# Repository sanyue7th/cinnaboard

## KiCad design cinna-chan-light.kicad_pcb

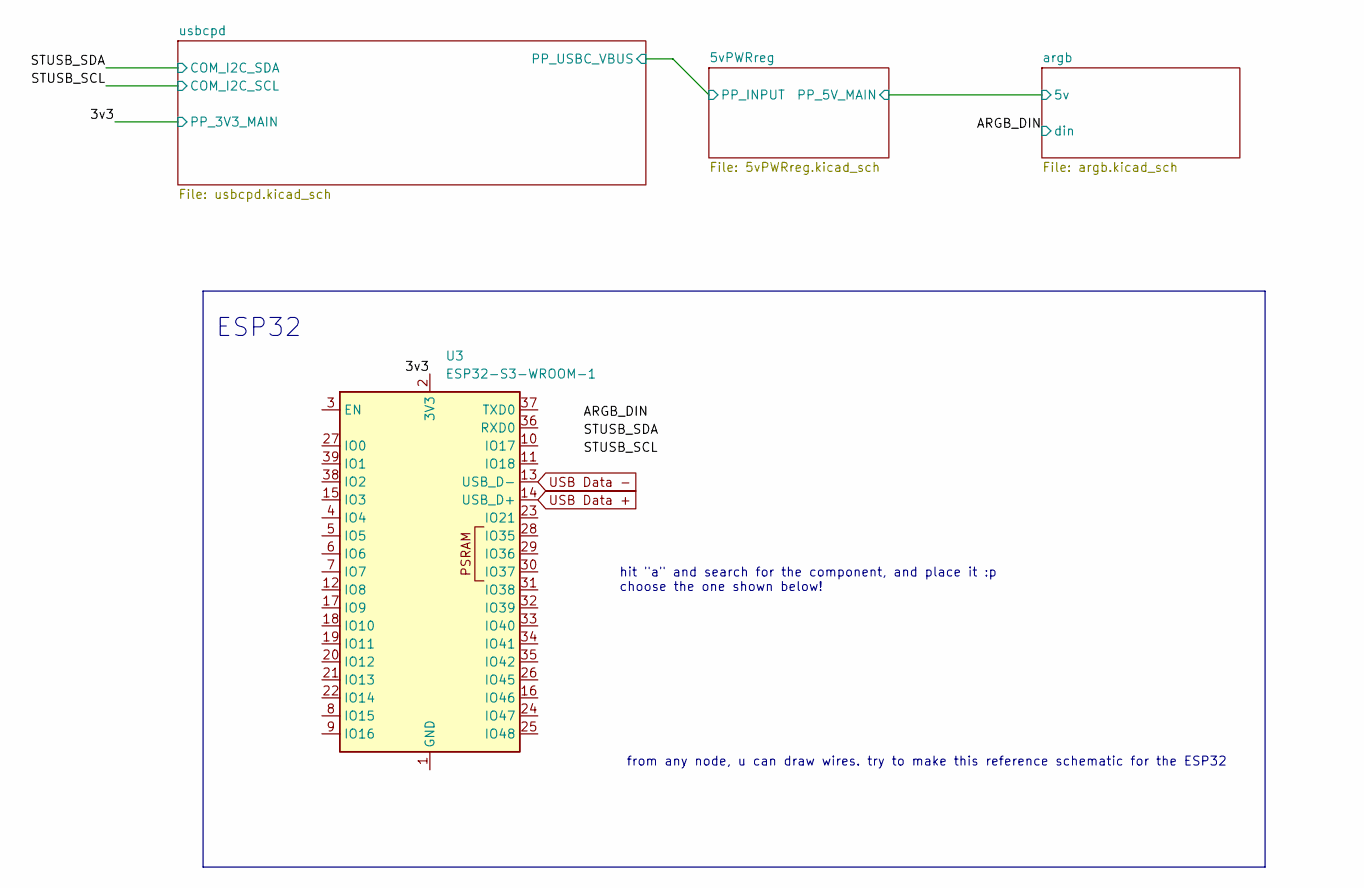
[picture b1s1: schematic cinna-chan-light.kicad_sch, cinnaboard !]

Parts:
U3: ESP32-S3-WROOM-1; LCSC C2913192

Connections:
unnamed: U3.1 (GND), U3.40 (GND), U3.41 (GND)

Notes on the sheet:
hit "a" and search for the component, and place it :p choose the one shown below!
ESP32
from any node, u can draw wires. try to make this reference schematic for the ESP32

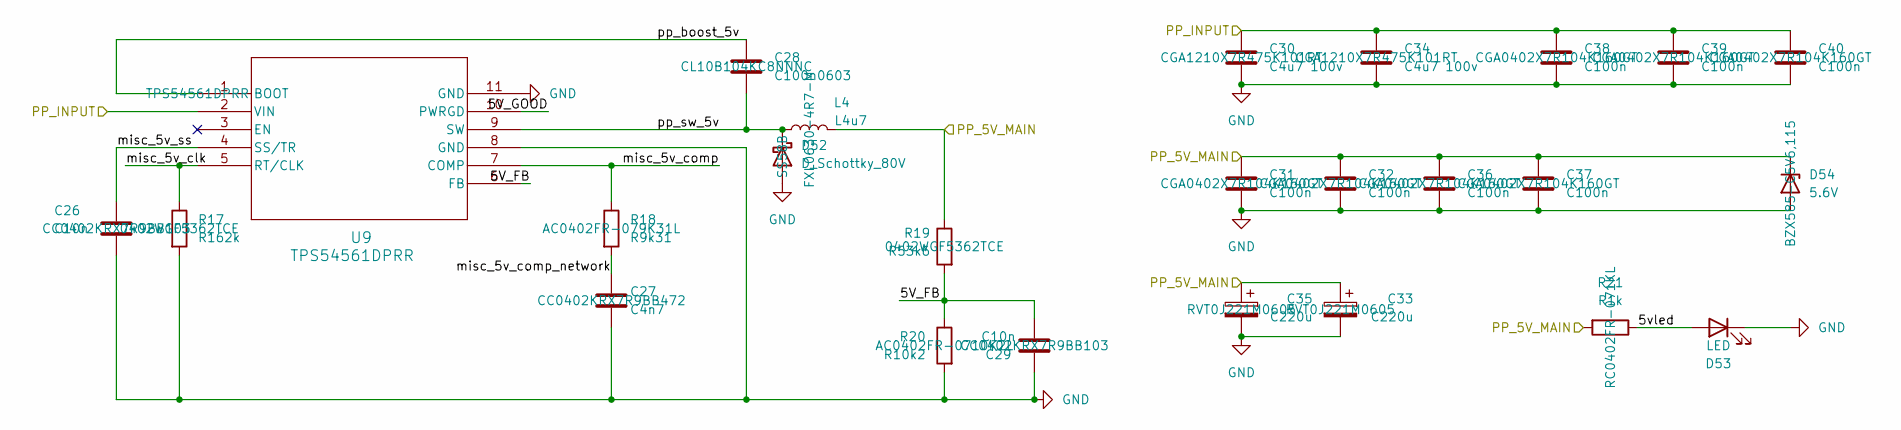
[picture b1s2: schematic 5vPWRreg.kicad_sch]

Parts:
C26, C29: C10n; C_0402_1005Metric
C27: C4n7; C_0402_1005Metric
C28: C100n0603; C_0603_1608Metric
C30, C34: C4u7 100v; L_1210_3225Metric
C31, C32, C36, C37, C38, C39, C40: C100n; C_0402_1005Metric
C33, C35: C220u; CP_Elec_6.3x5.4
D52: D_Schottky_80V; D_SMB
D53: LED; LED_0603_1608Metric
D54: 5.6V; D_SOD-523
L4: L4u7; L_Sunlord_MWSA0603S
R17: R162k; R_0402_1005Metric
R18: R9k31; R_0402_1005Metric
R19: R53k6; R_0402_1005Metric
R20: R10k2; R_0402_1005Metric
R21: R1k; R_0402_1005Metric
U9: TPS54561DPRR; WSON10_DPR_TEX

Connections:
/5vPWRreg/5V_FB: C29.1, R19.2, R20.1, U9.6 (FB)
/5vPWRreg/5V_GOOD: U9.10 (PWRGD)
/5vPWRreg/5vled: D53.2 (A), R21.1
/5vPWRreg/PP_5V_MAIN: C31.1, C32.1, C33.1, C35.1, C36.1, C37.1, D54.1 (K), L4.2, R19.1, R21.2; also elsewhere on the board
/5vPWRreg/PP_INPUT: C30.1, C34.1, C38.1, C39.1, C40.1, U9.2 (VIN)
/5vPWRreg/misc_5v_clk: R17.1, U9.5 (RT/CLK)
/5vPWRreg/misc_5v_comp: R18.1, U9.7 (COMP)
/5vPWRreg/misc_5v_comp_network: C27.2, R18.2
/5vPWRreg/misc_5v_ss: C26.2, U9.4 (SS/TR)
/5vPWRreg/pp_boost_5v: C28.1, U9.1 (BOOT)
/5vPWRreg/pp_sw_5v: C28.2, D52.1 (K), L4.1, U9.9 (SW)
GND: C26.1, C27.1, C29.2, C30.2, C31.2, C32.2, C33.2, C34.2, C35.2, C36.2, C37.2, C38.2, C39.2, C40.2, D52.2 (A), D53.1 (K), D54.2 (A), R17.2, R20.2, U9.8 (GND), U9.11 (GND); also elsewhere on the board

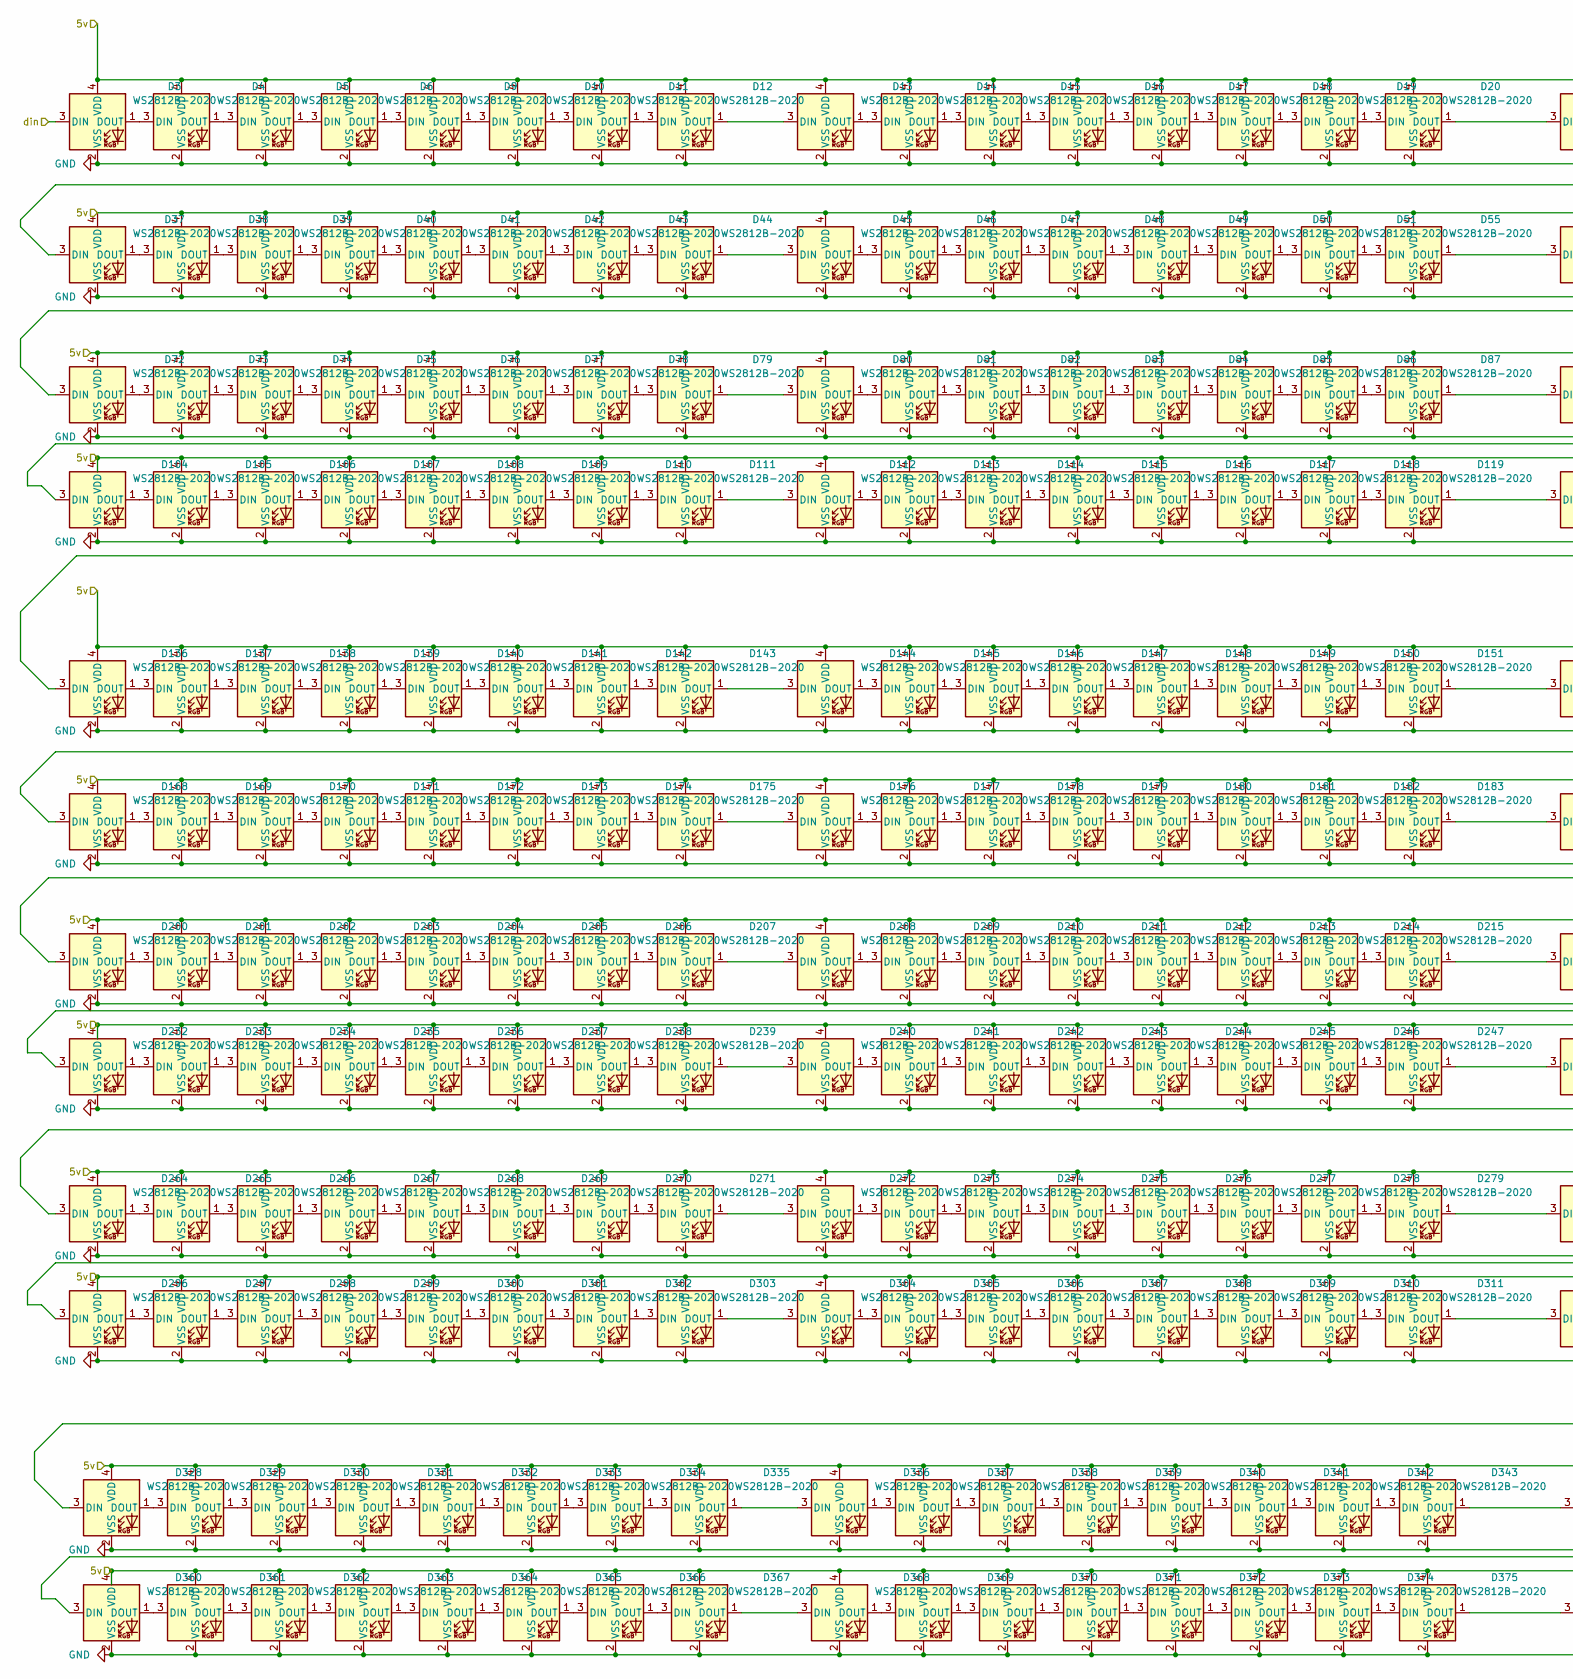
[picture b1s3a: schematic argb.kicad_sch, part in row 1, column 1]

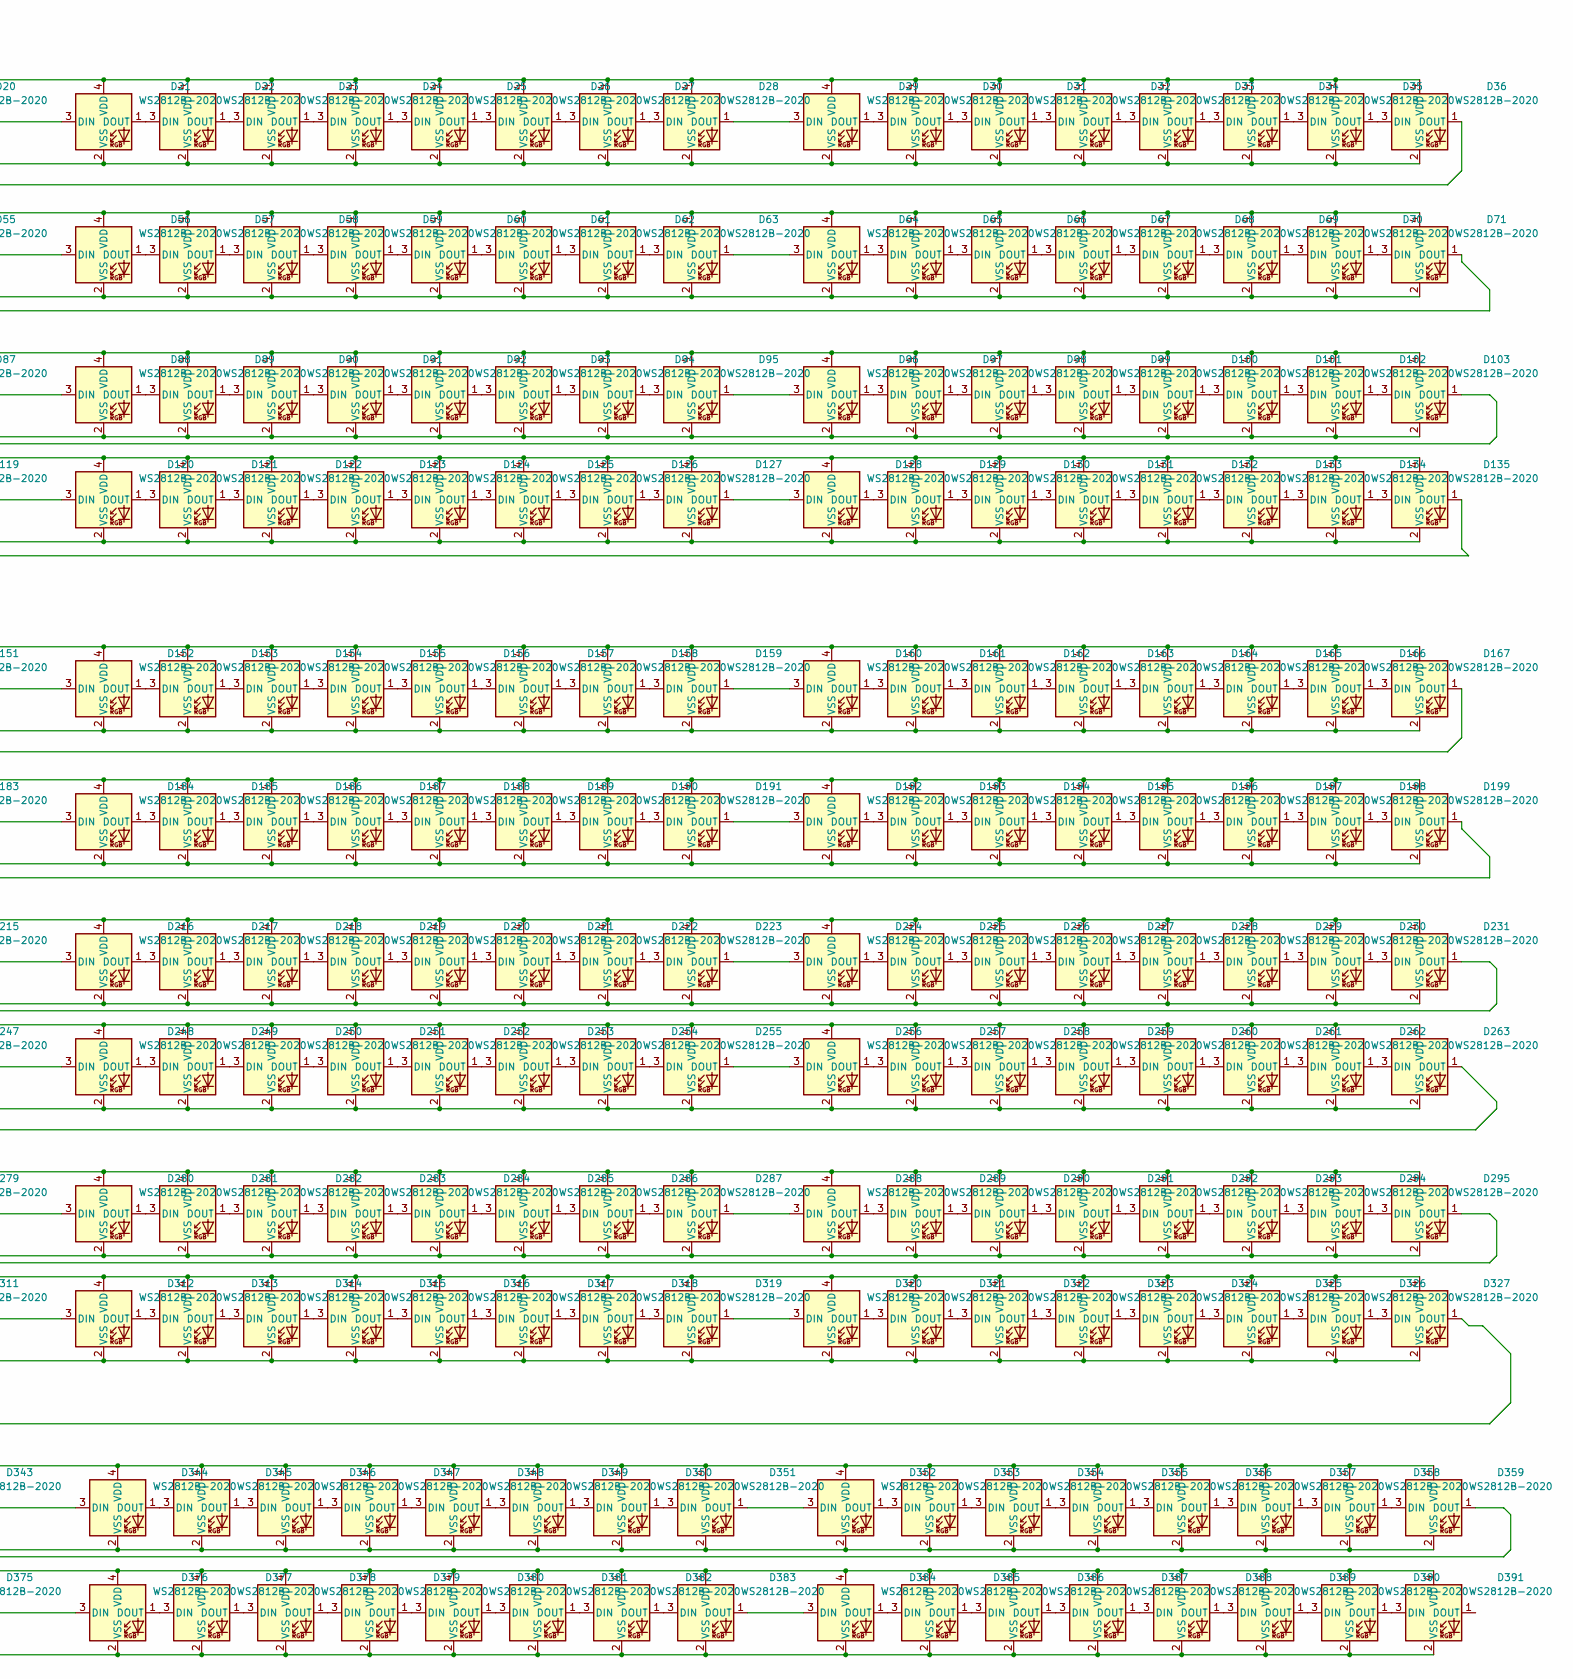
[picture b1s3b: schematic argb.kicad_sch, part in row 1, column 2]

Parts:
D3, D4, D5, D6, D9, D10, D11, D12, D13, D14, D15, D16, D17, D18, D19, D20, D21, D22, D23, D24, D25, D26, D27, D28, D29, D30, D31, D32, D33, D34, D35, D36, D37, D38, D39, D40, D41, D42, D43, D44, D45, D46, D47, D48, D49, D50, D51, D55, D56, D57, D58, D59, D60, D61, D62, D63, D64, D65, D66, D67, D68, D69, D70, D71, D72, D73, D74, D75, D76, D77, D78, D79, D80, D81, D82, D83, D84, D85, D86, D87, D88, D89, D90, D91, D92, D93, D94, D95, D96, D97, D98, D99, D100, D101, D102, D103, D104, D105, D106, D107, D108, D109, D110, D111, D112, D113, D114, D115, D116, D117, D118, D119, D120, D121, D122, D123, D124, D125, D126, D127, D128, D129, D130, D131, D132, D133, D134, D135, D136, D137, D138, D139, D140, D141, D142, D143, D144, D145, D146, D147, D148, D149, D150, D151, D152, D153, D154, D155, D156, D157, D158, D159, D160, D161, D162, D163, D164, D165, D166, D167, D168, D169, D170, D171, D172, D173, D174, D175, D176, D177, D178, D179, D180, D181, D182, D183, D184, D185, D186, D187, D188, D189, D190, D191, D192, D193, D194, D195, D196, D197, D198, D199, D200, D201, D202, D203, D204, D205, D206, D207, D208, D209, D210, D211, D212, D213, D214, D215, D216, D217, D218, D219, D220, D221, D222, D223, D224, D225, D226, D227, D228, D229, D230, D231, D232, D233, D234, D235, D236, D237, D238, D239, D240, D241, D242, D243, D244, D245, D246, D247, D248, D249, D250, D251, D252, D253, D254, D255, D256, D257, D258, D259, D260, D261, D262, D263, D264, D265, D266, D267, D268, D269, D270, D271, D272, D273, D274, D275, D276, D277, D278, D279, D280, D281, D282, D283, D284, D285, D286, D287, D288, D289, D290, D291, D292, D293, D294, D295, D296, D297, D298, D299, D300, D301, D302, D303, D304, D305, D306, D307, D308, D309, D310, D311, D312, D313, D314, D315, D316, D317, D318, D319, D320, D321, D322, D323, D324, D325, D326, D327, D328, D329, D330, D331, D332, D333, D334, D335, D336, D337, D338, D339, D340, D341, D342, D343, D344, D345, D346, D347, D348, D349, D350, D351, D352, D353, D354, D355, D356, D357, D358, D359, D360, D361, D362, D363, D364, D365, D366, D367, D368, D369, D370, D371, D372, D373, D374, D375, D376, D377, D378, D379, D380, D381, D382, D383, D384, D385, D386, D387, D388, D389, D390, D391: WS2812B-2020; LED_WS2812B-2020_PLCC4_2.0x2.0mm

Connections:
/5vPWRreg/PP_5V_MAIN: D3.4 (VDD), D4.4 (VDD), D5.4 (VDD), D6.4 (VDD), D9.4 (VDD), D10.4 (VDD), D11.4 (VDD), D12.4 (VDD), D13.4 (VDD), D14.4 (VDD), D15.4 (VDD), D16.4 (VDD), D17.4 (VDD), D18.4 (VDD), D19.4 (VDD), D20.4 (VDD), D21.4 (VDD), D22.4 (VDD), D23.4 (VDD), D24.4 (VDD), D25.4 (VDD), D26.4 (VDD), D27.4 (VDD), D28.4 (VDD), D29.4 (VDD), D30.4 (VDD), D31.4 (VDD), D32.4 (VDD), D33.4 (VDD), D34.4 (VDD), D35.4 (VDD), D36.4 (VDD), D37.4 (VDD), D38.4 (VDD), D39.4 (VDD), D40.4 (VDD), D41.4 (VDD), D42.4 (VDD), D43.4 (VDD), D44.4 (VDD), D45.4 (VDD), D46.4 (VDD), D47.4 (VDD), D48.4 (VDD), D49.4 (VDD), D50.4 (VDD), D51.4 (VDD), D55.4 (VDD), D56.4 (VDD), D57.4 (VDD), D58.4 (VDD), D59.4 (VDD), D60.4 (VDD), D61.4 (VDD), D62.4 (VDD), D63.4 (VDD), D64.4 (VDD), D65.4 (VDD), D66.4 (VDD), D67.4 (VDD), D68.4 (VDD), D69.4 (VDD), D70.4 (VDD), D71.4 (VDD), D72.4 (VDD), D73.4 (VDD), D74.4 (VDD), D75.4 (VDD), D76.4 (VDD), D77.4 (VDD), D78.4 (VDD), D79.4 (VDD), D80.4 (VDD), D81.4 (VDD), D82.4 (VDD), D83.4 (VDD), D84.4 (VDD), D85.4 (VDD), D86.4 (VDD), D87.4 (VDD), D88.4 (VDD), D89.4 (VDD), D90.4 (VDD), D91.4 (VDD), D92.4 (VDD), D93.4 (VDD), D94.4 (VDD), D95.4 (VDD), D96.4 (VDD), D97.4 (VDD), D98.4 (VDD), D99.4 (VDD), D100.4 (VDD), D101.4 (VDD), D102.4 (VDD), D103.4 (VDD), D104.4 (VDD), D105.4 (VDD), D106.4 (VDD), D107.4 (VDD), D108.4 (VDD), D109.4 (VDD), D110.4 (VDD), D111.4 (VDD), D112.4 (VDD), D113.4 (VDD), D114.4 (VDD), D115.4 (VDD), D116.4 (VDD), D117.4 (VDD), D118.4 (VDD), D119.4 (VDD), D120.4 (VDD), D121.4 (VDD), D122.4 (VDD), D123.4 (VDD), D124.4 (VDD), D125.4 (VDD), D126.4 (VDD), D127.4 (VDD), D128.4 (VDD), D129.4 (VDD), D130.4 (VDD), D131.4 (VDD), D132.4 (VDD), D133.4 (VDD), D134.4 (VDD), D135.4 (VDD), D136.4 (VDD), D137.4 (VDD), D138.4 (VDD), D139.4 (VDD), D140.4 (VDD), D141.4 (VDD), D142.4 (VDD), D143.4 (VDD), D144.4 (VDD), D145.4 (VDD), D146.4 (VDD), D147.4 (VDD), D148.4 (VDD), D149.4 (VDD), D150.4 (VDD), D151.4 (VDD), D152.4 (VDD), D153.4 (VDD), D154.4 (VDD), D155.4 (VDD), D156.4 (VDD), D157.4 (VDD), D158.4 (VDD), D159.4 (VDD), D160.4 (VDD), D161.4 (VDD), D162.4 (VDD), D163.4 (VDD), D164.4 (VDD), D165.4 (VDD), D166.4 (VDD), D167.4 (VDD), D168.4 (VDD), D169.4 (VDD), D170.4 (VDD), D171.4 (VDD), D172.4 (VDD), D173.4 (VDD), D174.4 (VDD), D175.4 (VDD), D176.4 (VDD), D177.4 (VDD), D178.4 (VDD), D179.4 (VDD), D180.4 (VDD), D181.4 (VDD), D182.4 (VDD), D183.4 (VDD), D184.4 (VDD), D185.4 (VDD), D186.4 (VDD), D187.4 (VDD), D188.4 (VDD), D189.4 (VDD), D190.4 (VDD), D191.4 (VDD), D192.4 (VDD), D193.4 (VDD), D194.4 (VDD), D195.4 (VDD), D196.4 (VDD), D197.4 (VDD), D198.4 (VDD), D199.4 (VDD), D200.4 (VDD), D201.4 (VDD), D202.4 (VDD), D203.4 (VDD), D204.4 (VDD), D205.4 (VDD), D206.4 (VDD), D207.4 (VDD), D208.4 (VDD), D209.4 (VDD), D210.4 (VDD), D211.4 (VDD), D212.4 (VDD), D213.4 (VDD), D214.4 (VDD), D215.4 (VDD), D216.4 (VDD), D217.4 (VDD), D218.4 (VDD), D219.4 (VDD), D220.4 (VDD), D221.4 (VDD), D222.4 (VDD), D223.4 (VDD), D224.4 (VDD), D225.4 (VDD), D226.4 (VDD), D227.4 (VDD), D228.4 (VDD), D229.4 (VDD), D230.4 (VDD), D231.4 (VDD), D232.4 (VDD), D233.4 (VDD), D234.4 (VDD), D235.4 (VDD), D236.4 (VDD), D237.4 (VDD), D238.4 (VDD), D239.4 (VDD), D240.4 (VDD), D241.4 (VDD), D242.4 (VDD), D243.4 (VDD), D244.4 (VDD), D245.4 (VDD), D246.4 (VDD), D247.4 (VDD), D248.4 (VDD), D249.4 (VDD), D250.4 (VDD), D251.4 (VDD), D252.4 (VDD), D253.4 (VDD), D254.4 (VDD), D255.4 (VDD), D256.4 (VDD), D257.4 (VDD), D258.4 (VDD), D259.4 (VDD), D260.4 (VDD), D261.4 (VDD), D262.4 (VDD), D263.4 (VDD), D264.4 (VDD), D265.4 (VDD), D266.4 (VDD), D267.4 (VDD), D268.4 (VDD), D269.4 (VDD), D270.4 (VDD), D271.4 (VDD), D272.4 (VDD), D273.4 (VDD), D274.4 (VDD)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; also elsewhere on the board
/argb/din: D3.3 (DIN)
GND: D3.2 (VSS), D4.2 (VSS), D5.2 (VSS), D6.2 (VSS), D9.2 (VSS), D10.2 (VSS), D11.2 (VSS), D12.2 (VSS), D13.2 (VSS), D14.2 (VSS), D15.2 (VSS), D16.2 (VSS), D17.2 (VSS), D18.2 (VSS), D19.2 (VSS), D20.2 (VSS), D21.2 (VSS), D22.2 (VSS), D23.2 (VSS), D24.2 (VSS), D25.2 (VSS), D26.2 (VSS), D27.2 (VSS), D28.2 (VSS), D29.2 (VSS), D30.2 (VSS), D31.2 (VSS), D32.2 (VSS), D33.2 (VSS), D34.2 (VSS), D35.2 (VSS), D36.2 (VSS), D37.2 (VSS), D38.2 (VSS), D39.2 (VSS), D40.2 (VSS), D41.2 (VSS), D42.2 (VSS), D43.2 (VSS), D44.2 (VSS), D45.2 (VSS), D46.2 (VSS), D47.2 (VSS), D48.2 (VSS), D49.2 (VSS), D50.2 (VSS), D51.2 (VSS), D55.2 (VSS), D56.2 (VSS), D57.2 (VSS), D58.2 (VSS), D59.2 (VSS), D60.2 (VSS), D61.2 (VSS), D62.2 (VSS), D63.2 (VSS), D64.2 (VSS), D65.2 (VSS), D66.2 (VSS), D67.2 (VSS), D68.2 (VSS), D69.2 (VSS), D70.2 (VSS), D71.2 (VSS), D72.2 (VSS), D73.2 (VSS), D74.2 (VSS), D75.2 (VSS), D76.2 (VSS), D77.2 (VSS), D78.2 (VSS), D79.2 (VSS), D80.2 (VSS), D81.2 (VSS), D82.2 (VSS), D83.2 (VSS), D84.2 (VSS), D85.2 (VSS), D86.2 (VSS), D87.2 (VSS), D88.2 (VSS), D89.2 (VSS), D90.2 (VSS), D91.2 (VSS), D92.2 (VSS), D93.2 (VSS), D94.2 (VSS), D95.2 (VSS), D96.2 (VSS), D97.2 (VSS), D98.2 (VSS), D99.2 (VSS), D100.2 (VSS), D101.2 (VSS), D102.2 (VSS), D103.2 (VSS), D104.2 (VSS), D105.2 (VSS), D106.2 (VSS), D107.2 (VSS), D108.2 (VSS), D109.2 (VSS), D110.2 (VSS), D111.2 (VSS), D112.2 (VSS), D113.2 (VSS), D114.2 (VSS), D115.2 (VSS), D116.2 (VSS), D117.2 (VSS), D118.2 (VSS), D119.2 (VSS), D120.2 (VSS), D121.2 (VSS), D122.2 (VSS), D123.2 (VSS), D124.2 (VSS), D125.2 (VSS), D126.2 (VSS), D127.2 (VSS), D128.2 (VSS), D129.2 (VSS), D130.2 (VSS), D131.2 (VSS), D132.2 (VSS), D133.2 (VSS), D134.2 (VSS), D135.2 (VSS), D136.2 (VSS), D137.2 (VSS), D138.2 (VSS), D139.2 (VSS), D140.2 (VSS), D141.2 (VSS), D142.2 (VSS), D143.2 (VSS), D144.2 (VSS), D145.2 (VSS), D146.2 (VSS), D147.2 (VSS), D148.2 (VSS), D149.2 (VSS), D150.2 (VSS), D151.2 (VSS), D152.2 (VSS), D153.2 (VSS), D154.2 (VSS), D155.2 (VSS), D156.2 (VSS), D157.2 (VSS), D158.2 (VSS), D159.2 (VSS), D160.2 (VSS), D161.2 (VSS), D162.2 (VSS), D163.2 (VSS), D164.2 (VSS), D165.2 (VSS), D166.2 (VSS), D167.2 (VSS), D168.2 (VSS), D169.2 (VSS), D170.2 (VSS), D171.2 (VSS), D172.2 (VSS), D173.2 (VSS), D174.2 (VSS), D175.2 (VSS), D176.2 (VSS), D177.2 (VSS), D178.2 (VSS), D179.2 (VSS), D180.2 (VSS), D181.2 (VSS), D182.2 (VSS), D183.2 (VSS), D184.2 (VSS), D185.2 (VSS), D186.2 (VSS), D187.2 (VSS), D188.2 (VSS), D189.2 (VSS), D190.2 (VSS), D191.2 (VSS), D192.2 (VSS), D193.2 (VSS), D194.2 (VSS), D195.2 (VSS), D196.2 (VSS), D197.2 (VSS), D198.2 (VSS), D199.2 (VSS), D200.2 (VSS), D201.2 (VSS), D202.2 (VSS), D203.2 (VSS), D204.2 (VSS), D205.2 (VSS), D206.2 (VSS), D207.2 (VSS), D208.2 (VSS), D209.2 (VSS), D210.2 (VSS), D211.2 (VSS), D212.2 (VSS), D213.2 (VSS), D214.2 (VSS), D215.2 (VSS), D216.2 (VSS), D217.2 (VSS), D218.2 (VSS), D219.2 (VSS), D220.2 (VSS), D221.2 (VSS), D222.2 (VSS), D223.2 (VSS), D224.2 (VSS), D225.2 (VSS), D226.2 (VSS), D227.2 (VSS), D228.2 (VSS), D229.2 (VSS), D230.2 (VSS), D231.2 (VSS), D232.2 (VSS), D233.2 (VSS), D234.2 (VSS), D235.2 (VSS), D236.2 (VSS), D237.2 (VSS), D238.2 (VSS), D239.2 (VSS), D240.2 (VSS), D241.2 (VSS), D242.2 (VSS), D243.2 (VSS), D244.2 (VSS), D245.2 (VSS), D246.2 (VSS), D247.2 (VSS), D248.2 (VSS), D249.2 (VSS), D250.2 (VSS), D251.2 (VSS), D252.2 (VSS), D253.2 (VSS), D254.2 (VSS), D255.2 (VSS), D256.2 (VSS), D257.2 (VSS), D258.2 (VSS), D259.2 (VSS), D260.2 (VSS), D261.2 (VSS), D262.2 (VSS), D263.2 (VSS), D264.2 (VSS), D265.2 (VSS), D266.2 (VSS), D267.2 (VSS), D268.2 (VSS), D269.2 (VSS), D270.2 (VSS), D271.2 (VSS), D272.2 (VSS), D273.2 (VSS), D274.2 (VSS)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; also elsewhere on the board
unnamed: D3.1 (DOUT), D4.3 (DIN)
unnamed: D4.1 (DOUT), D5.3 (DIN)
unnamed: D5.1 (DOUT), D6.3 (DIN)
unnamed: D6.1 (DOUT), D9.3 (DIN)
unnamed: D9.1 (DOUT), D10.3 (DIN)
unnamed: D10.1 (DOUT), D11.3 (DIN)
unnamed: D11.1 (DOUT), D12.3 (DIN)
unnamed: D12.1 (DOUT), D13.3 (DIN)
unnamed: D13.1 (DOUT), D14.3 (DIN)
unnamed: D14.1 (DOUT), D15.3 (DIN)
unnamed: D15.1 (DOUT), D16.3 (DIN)
unnamed: D16.1 (DOUT), D17.3 (DIN)
unnamed: D17.1 (DOUT), D18.3 (DIN)
unnamed: D18.1 (DOUT), D19.3 (DIN)
unnamed: D19.1 (DOUT), D20.3 (DIN)
unnamed: D20.1 (DOUT), D21.3 (DIN)
unnamed: D21.1 (DOUT), D22.3 (DIN)
unnamed: D22.1 (DOUT), D23.3 (DIN)
unnamed: D23.1 (DOUT), D24.3 (DIN)
unnamed: D24.1 (DOUT), D25.3 (DIN)
unnamed: D25.1 (DOUT), D26.3 (DIN)
unnamed: D26.1 (DOUT), D27.3 (DIN)
unnamed: D27.1 (DOUT), D28.3 (DIN)
unnamed: D28.1 (DOUT), D29.3 (DIN)
unnamed: D29.1 (DOUT), D30.3 (DIN)
unnamed: D30.1 (DOUT), D31.3 (DIN)
unnamed: D31.1 (DOUT), D32.3 (DIN)
unnamed: D32.1 (DOUT), D33.3 (DIN)
unnamed: D33.1 (DOUT), D34.3 (DIN)
unnamed: D34.1 (DOUT), D35.3 (DIN)
unnamed: D35.1 (DOUT), D36.3 (DIN)
unnamed: D36.1 (DOUT), D37.3 (DIN)
unnamed: D37.1 (DOUT), D38.3 (DIN)
unnamed: D38.1 (DOUT), D39.3 (DIN)
unnamed: D39.1 (DOUT), D40.3 (DIN)
unnamed: D40.1 (DOUT), D41.3 (DIN)
unnamed: D41.1 (DOUT), D42.3 (DIN)
unnamed: D42.1 (DOUT), D43.3 (DIN)
unnamed: D43.1 (DOUT), D44.3 (DIN)
unnamed: D44.1 (DOUT), D45.3 (DIN)
unnamed: D45.1 (DOUT), D46.3 (DIN)
unnamed: D46.1 (DOUT), D47.3 (DIN)
unnamed: D47.1 (DOUT), D48.3 (DIN)
unnamed: D48.1 (DOUT), D49.3 (DIN)
unnamed: D49.1 (DOUT), D50.3 (DIN)
unnamed: D50.1 (DOUT), D51.3 (DIN)
unnamed: D51.1 (DOUT), D55.3 (DIN)
unnamed: D55.1 (DOUT), D56.3 (DIN)
unnamed: D56.1 (DOUT), D57.3 (DIN)
unnamed: D57.1 (DOUT), D58.3 (DIN)
unnamed: D58.1 (DOUT), D59.3 (DIN)
unnamed: D59.1 (DOUT), D60.3 (DIN)
unnamed: D60.1 (DOUT), D61.3 (DIN)
unnamed: D61.1 (DOUT), D62.3 (DIN)
unnamed: D62.1 (DOUT), D63.3 (DIN)
unnamed: D63.1 (DOUT), D64.3 (DIN)
unnamed: D64.1 (DOUT), D65.3 (DIN)
unnamed: D65.1 (DOUT), D66.3 (DIN)
unnamed: D66.1 (DOUT), D67.3 (DIN)
unnamed: D67.1 (DOUT), D68.3 (DIN)
unnamed: D68.1 (DOUT), D69.3 (DIN)
unnamed: D69.1 (DOUT), D70.3 (DIN)
unnamed: D70.1 (DOUT), D71.3 (DIN)
unnamed: D71.1 (DOUT), D72.3 (DIN)
unnamed: D72.1 (DOUT), D73.3 (DIN)
unnamed: D73.1 (DOUT), D74.3 (DIN)
unnamed: D74.1 (DOUT), D75.3 (DIN)
unnamed: D75.1 (DOUT), D76.3 (DIN)
unnamed: D76.1 (DOUT), D77.3 (DIN)
unnamed: D77.1 (DOUT), D78.3 (DIN)
unnamed: D78.1 (DOUT), D79.3 (DIN)
unnamed: D79.1 (DOUT), D80.3 (DIN)
unnamed: D80.1 (DOUT), D81.3 (DIN)
unnamed: D81.1 (DOUT), D82.3 (DIN)
unnamed: D82.1 (DOUT), D83.3 (DIN)
unnamed: D83.1 (DOUT), D84.3 (DIN)
unnamed: D84.1 (DOUT), D85.3 (DIN)
unnamed: D85.1 (DOUT), D86.3 (DIN)
unnamed: D86.1 (DOUT), D87.3 (DIN)
unnamed: D87.1 (DOUT), D88.3 (DIN)
unnamed: D88.1 (DOUT), D89.3 (DIN)
unnamed: D89.1 (DOUT), D90.3 (DIN)
unnamed: D90.1 (DOUT), D91.3 (DIN)
unnamed: D91.1 (DOUT), D92.3 (DIN)
unnamed: D92.1 (DOUT), D93.3 (DIN)
unnamed: D93.1 (DOUT), D94.3 (DIN)
unnamed: D94.1 (DOUT), D95.3 (DIN)
unnamed: D95.1 (DOUT), D96.3 (DIN)
unnamed: D96.1 (DOUT), D97.3 (DIN)
unnamed: D97.1 (DOUT), D98.3 (DIN)
unnamed: D98.1 (DOUT), D99.3 (DIN)
unnamed: D99.1 (DOUT), D100.3 (DIN)
unnamed: D100.1 (DOUT), D101.3 (DIN)
unnamed: D101.1 (DOUT), D102.3 (DIN)
unnamed: D102.1 (DOUT), D103.3 (DIN)
unnamed: D103.1 (DOUT), D104.3 (DIN)
unnamed: D104.1 (DOUT), D105.3 (DIN)
unnamed: D105.1 (DOUT), D106.3 (DIN)
unnamed: D106.1 (DOUT), D107.3 (DIN)
unnamed: D107.1 (DOUT), D108.3 (DIN)
unnamed: D108.1 (DOUT), D109.3 (DIN)
unnamed: D109.1 (DOUT), D110.3 (DIN)
unnamed: D110.1 (DOUT), D111.3 (DIN)
unnamed: D111.1 (DOUT), D112.3 (DIN)
unnamed: D112.1 (DOUT), D113.3 (DIN)
unnamed: D113.1 (DOUT), D114.3 (DIN)
unnamed: D114.1 (DOUT), D115.3 (DIN)
unnamed: D115.1 (DOUT), D116.3 (DIN)
unnamed: D116.1 (DOUT), D117.3 (DIN)
unnamed: D117.1 (DOUT), D118.3 (DIN)
unnamed: D118.1 (DOUT), D119.3 (DIN)
unnamed: D119.1 (DOUT), D120.3 (DIN)
unnamed: D120.1 (DOUT), D121.3 (DIN)
unnamed: D121.1 (DOUT), D122.3 (DIN)
unnamed: D122.1 (DOUT), D123.3 (DIN)
unnamed: D123.1 (DOUT), D124.3 (DIN)
unnamed: D124.1 (DOUT), D125.3 (DIN)
unnamed: D125.1 (DOUT), D126.3 (DIN)
unnamed: D126.1 (DOUT), D127.3 (DIN)
unnamed: D127.1 (DOUT), D128.3 (DIN)
unnamed: D128.1 (DOUT), D129.3 (DIN)
unnamed: D129.1 (DOUT), D130.3 (DIN)
unnamed: D130.1 (DOUT), D131.3 (DIN)
unnamed: D131.1 (DOUT), D132.3 (DIN)
unnamed: D132.1 (DOUT), D133.3 (DIN)
unnamed: D133.1 (DOUT), D134.3 (DIN)
unnamed: D134.1 (DOUT), D135.3 (DIN)
unnamed: D135.1 (DOUT), D136.3 (DIN)
unnamed: D136.1 (DOUT), D137.3 (DIN)
unnamed: D137.1 (DOUT), D138.3 (DIN)
unnamed: D138.1 (DOUT), D139.3 (DIN)
unnamed: D139.1 (DOUT), D140.3 (DIN)
unnamed: D140.1 (DOUT), D141.3 (DIN)
unnamed: D141.1 (DOUT), D142.3 (DIN)
unnamed: D142.1 (DOUT), D143.3 (DIN)
unnamed: D143.1 (DOUT), D144.3 (DIN)
unnamed: D144.1 (DOUT), D145.3 (DIN)
unnamed: D145.1 (DOUT), D146.3 (DIN)
unnamed: D146.1 (DOUT), D147.3 (DIN)
unnamed: D147.1 (DOUT), D148.3 (DIN)
unnamed: D148.1 (DOUT), D149.3 (DIN)
unnamed: D149.1 (DOUT), D150.3 (DIN)
unnamed: D150.1 (DOUT), D151.3 (DIN)
unnamed: D151.1 (DOUT), D152.3 (DIN)
unnamed: D152.1 (DOUT), D153.3 (DIN)
unnamed: D153.1 (DOUT), D154.3 (DIN)
unnamed: D154.1 (DOUT), D155.3 (DIN)
unnamed: D155.1 (DOUT), D156.3 (DIN)
unnamed: D156.1 (DOUT), D157.3 (DIN)
unnamed: D157.1 (DOUT), D158.3 (DIN)
unnamed: D158.1 (DOUT), D159.3 (DIN)
unnamed: D159.1 (DOUT), D160.3 (DIN)
unnamed: D160.1 (DOUT), D161.3 (DIN)
unnamed: D161.1 (DOUT), D162.3 (DIN)
unnamed: D162.1 (DOUT), D163.3 (DIN)
unnamed: D163.1 (DOUT), D164.3 (DIN)
unnamed: D164.1 (DOUT), D165.3 (DIN)
unnamed: D165.1 (DOUT), D166.3 (DIN)
unnamed: D166.1 (DOUT), D167.3 (DIN)
unnamed: D167.1 (DOUT), D168.3 (DIN)
unnamed: D168.1 (DOUT), D169.3 (DIN)
unnamed: D169.1 (DOUT), D170.3 (DIN)
unnamed: D170.1 (DOUT), D171.3 (DIN)
unnamed: D171.1 (DOUT), D172.3 (DIN)
unnamed: D172.1 (DOUT), D173.3 (DIN)
unnamed: D173.1 (DOUT), D174.3 (DIN)
unnamed: D174.1 (DOUT), D175.3 (DIN)
unnamed: D175.1 (DOUT), D176.3 (DIN)
unnamed: D176.1 (DOUT), D177.3 (DIN)
unnamed: D177.1 (DOUT), D178.3 (DIN)
unnamed: D178.1 (DOUT), D179.3 (DIN)
unnamed: D179.1 (DOUT), D180.3 (DIN)
unnamed: D180.1 (DOUT), D181.3 (DIN)
unnamed: D181.1 (DOUT), D182.3 (DIN)
unnamed: D182.1 (DOUT), D183.3 (DIN)
unnamed: D183.1 (DOUT), D184.3 (DIN)
unnamed: D184.1 (DOUT), D185.3 (DIN)
unnamed: D185.1 (DOUT), D186.3 (DIN)
unnamed: D186.1 (DOUT), D187.3 (DIN)
unnamed: D187.1 (DOUT), D188.3 (DIN)
unnamed: D188.1 (DOUT), D189.3 (DIN)
unnamed: D189.1 (DOUT), D190.3 (DIN)
unnamed: D190.1 (DOUT), D191.3 (DIN)
unnamed: D191.1 (DOUT), D192.3 (DIN)
unnamed: D192.1 (DOUT), D193.3 (DIN)
unnamed: D193.1 (DOUT), D194.3 (DIN)
unnamed: D194.1 (DOUT), D195.3 (DIN)
unnamed: D195.1 (DOUT), D196.3 (DIN)
unnamed: D196.1 (DOUT), D197.3 (DIN)
unnamed: D197.1 (DOUT), D198.3 (DIN)
unnamed: D198.1 (DOUT), D199.3 (DIN)
unnamed: D199.1 (DOUT), D200.3 (DIN)
unnamed: D200.1 (DOUT), D201.3 (DIN)
unnamed: D201.1 (DOUT), D202.3 (DIN)
unnamed: D202.1 (DOUT), D203.3 (DIN)
unnamed: D203.1 (DOUT), D204.3 (DIN)
unnamed: D204.1 (DOUT), D205.3 (DIN)
unnamed: D205.1 (DOUT), D206.3 (DIN)
unnamed: D206.1 (DOUT), D207.3 (DIN)
unnamed: D207.1 (DOUT), D208.3 (DIN)
unnamed: D208.1 (DOUT), D209.3 (DIN)
unnamed: D209.1 (DOUT), D210.3 (DIN)
unnamed: D210.1 (DOUT), D211.3 (DIN)
unnamed: D211.1 (DOUT), D212.3 (DIN)
unnamed: D212.1 (DOUT), D213.3 (DIN)
unnamed: D213.1 (DOUT), D214.3 (DIN)
unnamed: D214.1 (DOUT), D215.3 (DIN)
unnamed: D215.1 (DOUT), D216.3 (DIN)
unnamed: D216.1 (DOUT), D217.3 (DIN)
unnamed: D217.1 (DOUT), D218.3 (DIN)
unnamed: D218.1 (DOUT), D219.3 (DIN)
unnamed: D219.1 (DOUT), D220.3 (DIN)
unnamed: D220.1 (DOUT), D221.3 (DIN)
unnamed: D221.1 (DOUT), D222.3 (DIN)
unnamed: D222.1 (DOUT), D223.3 (DIN)
unnamed: D223.1 (DOUT), D224.3 (DIN)
unnamed: D224.1 (DOUT), D225.3 (DIN)
unnamed: D225.1 (DOUT), D226.3 (DIN)
unnamed: D226.1 (DOUT), D227.3 (DIN)
unnamed: D227.1 (DOUT), D228.3 (DIN)
unnamed: D228.1 (DOUT), D229.3 (DIN)
unnamed: D229.1 (DOUT), D230.3 (DIN)
unnamed: D230.1 (DOUT), D231.3 (DIN)
unnamed: D231.1 (DOUT), D232.3 (DIN)
unnamed: D232.1 (DOUT), D233.3 (DIN)
unnamed: D233.1 (DOUT), D234.3 (DIN)
unnamed: D234.1 (DOUT), D235.3 (DIN)
unnamed: D235.1 (DOUT), D236.3 (DIN)
unnamed: D236.1 (DOUT), D237.3 (DIN)
unnamed: D237.1 (DOUT), D238.3 (DIN)
unnamed: D238.1 (DOUT), D239.3 (DIN)
unnamed: D239.1 (DOUT), D240.3 (DIN)
unnamed: D240.1 (DOUT), D241.3 (DIN)
unnamed: D241.1 (DOUT), D242.3 (DIN)
unnamed: D242.1 (DOUT), D243.3 (DIN)
unnamed: D243.1 (DOUT), D244.3 (DIN)
unnamed: D244.1 (DOUT), D245.3 (DIN)
unnamed: D245.1 (DOUT), D246.3 (DIN)
unnamed: D246.1 (DOUT), D247.3 (DIN)
unnamed: D247.1 (DOUT), D248.3 (DIN)
unnamed: D248.1 (DOUT), D249.3 (DIN)
unnamed: D249.1 (DOUT), D250.3 (DIN)
unnamed: D250.1 (DOUT), D251.3 (DIN)
unnamed: D251.1 (DOUT), D252.3 (DIN)
unnamed: D252.1 (DOUT), D253.3 (DIN)
unnamed: D253.1 (DOUT), D254.3 (DIN)
unnamed: D254.1 (DOUT), D255.3 (DIN)
unnamed: D255.1 (DOUT), D256.3 (DIN)
unnamed: D256.1 (DOUT), D257.3 (DIN)
unnamed: D257.1 (DOUT), D258.3 (DIN)
unnamed: D258.1 (DOUT), D259.3 (DIN)
unnamed: D259.1 (DOUT), D260.3 (DIN)
unnamed: D260.1 (DOUT), D261.3 (DIN)
unnamed: D261.1 (DOUT), D262.3 (DIN)
unnamed: D262.1 (DOUT), D263.3 (DIN)
unnamed: D263.1 (DOUT), D264.3 (DIN)
unnamed: D264.1 (DOUT), D265.3 (DIN)
unnamed: D265.1 (DOUT), D266.3 (DIN)
unnamed: D266.1 (DOUT), D267.3 (DIN)
unnamed: D267.1 (DOUT), D268.3 (DIN)
unnamed: D268.1 (DOUT), D269.3 (DIN)
unnamed: D269.1 (DOUT), D270.3 (DIN)
unnamed: D270.1 (DOUT), D271.3 (DIN)
unnamed: D271.1 (DOUT), D272.3 (DIN)
unnamed: D272.1 (DOUT), D273.3 (DIN)
unnamed: D273.1 (DOUT), D274.3 (DIN)
unnamed: D274.1 (DOUT), D275.3 (DIN)
unnamed: D275.1 (DOUT), D276.3 (DIN)
unnamed: D276.1 (DOUT), D277.3 (DIN)
unnamed: D277.1 (DOUT), D278.3 (DIN)
unnamed: D278.1 (DOUT), D279.3 (DIN)
unnamed: D279.1 (DOUT), D280.3 (DIN)
unnamed: D280.1 (DOUT), D281.3 (DIN)
unnamed: D281.1 (DOUT), D282.3 (DIN)
unnamed: D282.1 (DOUT), D283.3 (DIN)
unnamed: D283.1 (DOUT), D284.3 (DIN)
unnamed: D284.1 (DOUT), D285.3 (DIN)
unnamed: D285.1 (DOUT), D286.3 (DIN)
unnamed: D286.1 (DOUT), D287.3 (DIN)
unnamed: D287.1 (DOUT), D288.3 (DIN)
unnamed: D288.1 (DOUT), D289.3 (DIN)
unnamed: D289.1 (DOUT), D290.3 (DIN)
unnamed: D290.1 (DOUT), D291.3 (DIN)
unnamed: D291.1 (DOUT), D292.3 (DIN)
unnamed: D292.1 (DOUT), D293.3 (DIN)
unnamed: D293.1 (DOUT), D294.3 (DIN)
unnamed: D294.1 (DOUT), D295.3 (DIN)
unnamed: D295.1 (DOUT), D296.3 (DIN)
unnamed: D296.1 (DOUT), D297.3 (DIN)
unnamed: D297.1 (DOUT), D298.3 (DIN)
unnamed: D298.1 (DOUT), D299.3 (DIN)
unnamed: D299.1 (DOUT), D300.3 (DIN)
unnamed: D300.1 (DOUT), D301.3 (DIN)
unnamed: D301.1 (DOUT), D302.3 (DIN)
unnamed: D302.1 (DOUT), D303.3 (DIN)
unnamed: D303.1 (DOUT), D304.3 (DIN)
unnamed: D304.1 (DOUT), D305.3 (DIN)
unnamed: D305.1 (DOUT), D306.3 (DIN)
unnamed: D306.1 (DOUT), D307.3 (DIN)
unnamed: D307.1 (DOUT), D308.3 (DIN)
unnamed: D308.1 (DOUT), D309.3 (DIN)
unnamed: D309.1 (DOUT), D310.3 (DIN)
unnamed: D310.1 (DOUT), D311.3 (DIN)
unnamed: D311.1 (DOUT), D312.3 (DIN)
unnamed: D312.1 (DOUT), D313.3 (DIN)
unnamed: D313.1 (DOUT), D314.3 (DIN)
unnamed: D314.1 (DOUT), D315.3 (DIN)
unnamed: D315.1 (DOUT), D316.3 (DIN)
unnamed: D316.1 (DOUT), D317.3 (DIN)
unnamed: D317.1 (DOUT), D318.3 (DIN)
unnamed: D318.1 (DOUT), D319.3 (DIN)
unnamed: D319.1 (DOUT), D320.3 (DIN)
unnamed: D320.1 (DOUT), D321.3 (DIN)
unnamed: D321.1 (DOUT), D322.3 (DIN)
unnamed: D322.1 (DOUT), D323.3 (DIN)
unnamed: D323.1 (DOUT), D324.3 (DIN)
unnamed: D324.1 (DOUT), D325.3 (DIN)
unnamed: D325.1 (DOUT), D326.3 (DIN)
unnamed: D326.1 (DOUT), D327.3 (DIN)
unnamed: D327.1 (DOUT), D328.3 (DIN)
unnamed: D328.1 (DOUT), D329.3 (DIN)
unnamed: D329.1 (DOUT), D330.3 (DIN)
unnamed: D330.1 (DOUT), D331.3 (DIN)
unnamed: D331.1 (DOUT), D332.3 (DIN)
unnamed: D332.1 (DOUT), D333.3 (DIN)
unnamed: D333.1 (DOUT), D334.3 (DIN)
unnamed: D334.1 (DOUT), D335.3 (DIN)
unnamed: D335.1 (DOUT), D336.3 (DIN)
unnamed: D336.1 (DOUT), D337.3 (DIN)
unnamed: D337.1 (DOUT), D338.3 (DIN)
unnamed: D338.1 (DOUT), D339.3 (DIN)
unnamed: D339.1 (DOUT), D340.3 (DIN)
unnamed: D340.1 (DOUT), D341.3 (DIN)
unnamed: D341.1 (DOUT), D342.3 (DIN)
unnamed: D342.1 (DOUT), D343.3 (DIN)
unnamed: D343.1 (DOUT), D344.3 (DIN)
unnamed: D344.1 (DOUT), D345.3 (DIN)
unnamed: D345.1 (DOUT), D346.3 (DIN)
unnamed: D346.1 (DOUT), D347.3 (DIN)
unnamed: D347.1 (DOUT), D348.3 (DIN)
unnamed: D348.1 (DOUT), D349.3 (DIN)
unnamed: D349.1 (DOUT), D350.3 (DIN)
unnamed: D350.1 (DOUT), D351.3 (DIN)
unnamed: D351.1 (DOUT), D352.3 (DIN)
unnamed: D352.1 (DOUT), D353.3 (DIN)
unnamed: D353.1 (DOUT), D354.3 (DIN)
unnamed: D354.1 (DOUT), D355.3 (DIN)
unnamed: D355.1 (DOUT), D356.3 (DIN)
unnamed: D356.1 (DOUT), D357.3 (DIN)
unnamed: D357.1 (DOUT), D358.3 (DIN)
unnamed: D358.1 (DOUT), D359.3 (DIN)
unnamed: D359.1 (DOUT), D360.3 (DIN)
unnamed: D360.1 (DOUT), D361.3 (DIN)
unnamed: D361.1 (DOUT), D362.3 (DIN)
unnamed: D362.1 (DOUT), D363.3 (DIN)
unnamed: D363.1 (DOUT), D364.3 (DIN)
unnamed: D364.1 (DOUT), D365.3 (DIN)
unnamed: D365.1 (DOUT), D366.3 (DIN)
unnamed: D366.1 (DOUT), D367.3 (DIN)
unnamed: D367.1 (DOUT), D368.3 (DIN)
unnamed: D368.1 (DOUT), D369.3 (DIN)
unnamed: D369.1 (DOUT), D370.3 (DIN)
unnamed: D370.1 (DOUT), D371.3 (DIN)
unnamed: D371.1 (DOUT), D372.3 (DIN)
unnamed: D372.1 (DOUT), D373.3 (DIN)
unnamed: D373.1 (DOUT), D374.3 (DIN)
unnamed: D374.1 (DOUT), D375.3 (DIN)
unnamed: D375.1 (DOUT), D376.3 (DIN)
unnamed: D376.1 (DOUT), D377.3 (DIN)
unnamed: D377.1 (DOUT), D378.3 (DIN)
unnamed: D378.1 (DOUT), D379.3 (DIN)
unnamed: D379.1 (DOUT), D380.3 (DIN)
unnamed: D380.1 (DOUT), D381.3 (DIN)
unnamed: D381.1 (DOUT), D382.3 (DIN)
unnamed: D382.1 (DOUT), D383.3 (DIN)
unnamed: D383.1 (DOUT), D384.3 (DIN)
unnamed: D384.1 (DOUT), D385.3 (DIN)
unnamed: D385.1 (DOUT), D386.3 (DIN)
unnamed: D386.1 (DOUT), D387.3 (DIN)
unnamed: D387.1 (DOUT), D388.3 (DIN)
unnamed: D388.1 (DOUT), D389.3 (DIN)
unnamed: D389.1 (DOUT), D390.3 (DIN)
unnamed: D390.1 (DOUT), D391.3 (DIN)

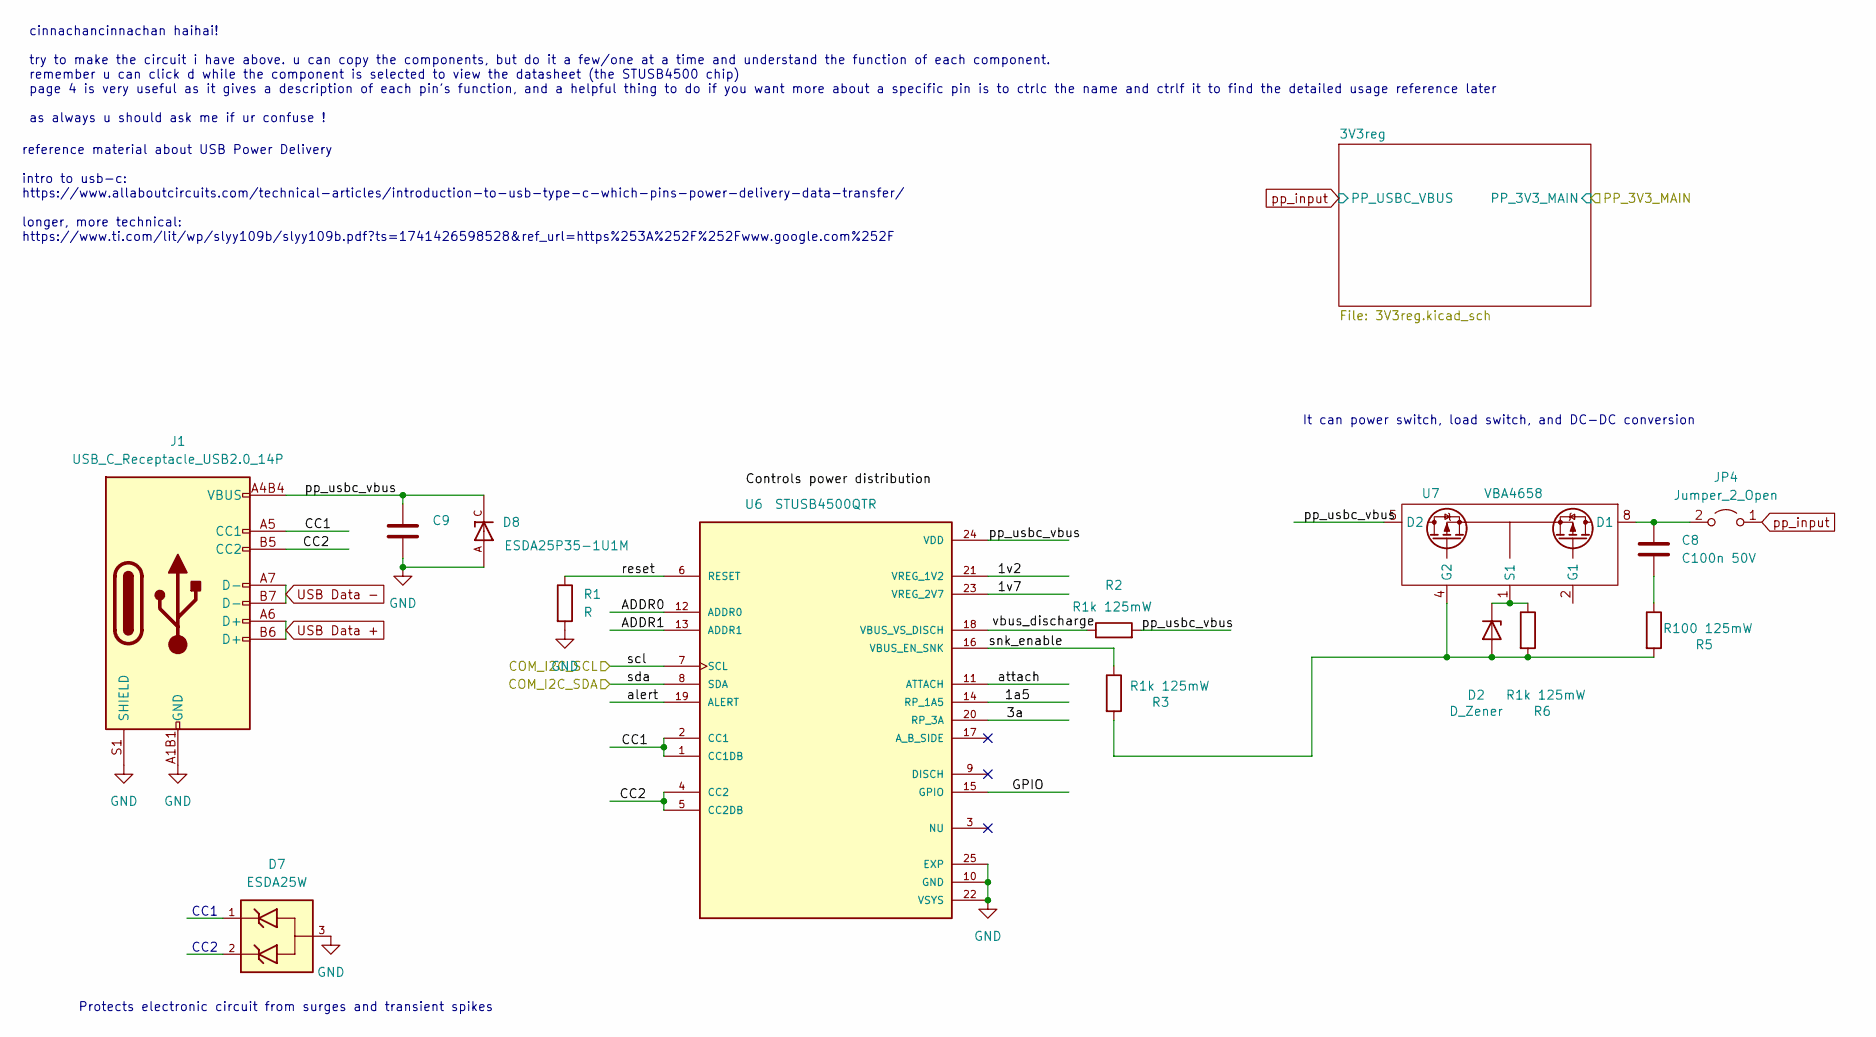
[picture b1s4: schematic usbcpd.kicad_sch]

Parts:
C8: C100n 50V; C_0201_0603Metric; LCSC C14663
C9: C; C_0201_0603Metric; LCSC C125977
D2: D_Zener; Littelfuse_PolyZen-LS; LCSC C5448546
D7: ESDA25W; SOT65P210X110-3N; LCSC C2935152
D8: ESDA25P35-1U1M; TVS_ESDA25P35-1U1M; LCSC C19829649
J1: USB_C_Receptacle_USB2.0_14P; USB_C_Receptacle_GCT_USB4105-xx-A_16P_TopMnt_Horizontal
JP4: Jumper_2_Open; SolderJumper-2_P1.3mm_Open_TrianglePad1.0x1.5mm
R1: R; R_0201_0603Metric; LCSC C98220
R2: R1k 125mW; R_0201_0603Metric; LCSC C5448546
R3, R6: R1k 125mW; R_0201_0603Metric; LCSC C98220
R5: R100 125mW; R_0201_0603Metric; LCSC C98220
U6: STUSB4500QTR; QFN50P400X400X100-25N; LCSC C2678061
U7: VBA4658; SO-8_3.9x4.9mm_P1.27mm; LCSC C416242

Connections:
/usbcpd/1a5: U6.14 (RP_1A5)
/usbcpd/1v2: U6.21 (VREG_1V2)
/usbcpd/1v7: U6.23 (VREG_2V7)
/usbcpd/3a: U6.20 (RP_3A)
/usbcpd/ADDR0: U6.12 (ADDR0)
/usbcpd/ADDR1: U6.13 (ADDR1)
/usbcpd/CC1: J1.A5 (CC1), U6.1 (CC1DB), U6.2 (CC1)
/usbcpd/CC2: J1.B5 (CC2), U6.4 (CC2), U6.5 (CC2DB)
/usbcpd/GPIO: U6.15 (GPIO)
/usbcpd/alert: U6.19 (ALERT)
/usbcpd/attach: U6.11 (ATTACH)
/usbcpd/pp_usbc_vbus: C9.1, D8.C, J1.A4B4 (VBUS), J1.A9 (VBUS), J1.B4 (VBUS), J1.B9 (VBUS), R2.2, U6.24 (VDD), U7.5 (D2), U7.6 (D2)
/usbcpd/reset: R1.1, U6.6 (RESET)
/usbcpd/scl: U6.7 (SCL)
/usbcpd/sda: U6.8 (SDA)
/usbcpd/snk_enable: R3.1, U6.16 (VBUS_EN_SNK)
GND: C9.2, D7.3, D8.A, J1.A1B1 (GND), J1.A12 (GND), J1.B1 (GND), J1.B12 (GND), J1.S1 (SHIELD), R1.2, U6.10 (GND), U6.22 (VSYS), U6.25 (EXP); also elsewhere on the board
unnamed: C8.2, R5.1
unnamed: D2.2 (A), R3.2, R5.2, R6.2, U7.4 (G2)
unnamed: D2.1 (K), R6.1, U7.1 (S1), U7.3 (S2)
unnamed: C8.1, JP4.2 (B), U7.7 (D1), U7.8 (D1)
unnamed: R2.1, U6.18 (VBUS_VS_DISCH)
USB Data +: J1.A6 (D+), J1.B6 (D+)
USB Data -: J1.A7 (D-), J1.B7 (D-)
pp_input: JP4.1 (A)

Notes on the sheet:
CC1
CC2
cinnachancinnachan haihai! try to make the circuit i have above. u can copy the components, but do it a few/one at a time and understand the function of each component. remember u can click d while the component is selected to view the datasheet (the STUSB4500 chip) page 4 is very useful as it give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
Protects electronic circuit from surges and transient spikes
reference material about USB Power Delivery intro to usb-c: https://www.allaboutcircuits.com/technical-articles/introduction-to-usb-type-c-which-pins-power-delivery-data-transfer/ longer, more technical: https://www.ti.com/lit/wp/slyy109b/slyy109b.pdf?ts=1741426598528&ref_url=https%253A%252F%252Fww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
It can power switch, load switch, and DC-DC conversion
